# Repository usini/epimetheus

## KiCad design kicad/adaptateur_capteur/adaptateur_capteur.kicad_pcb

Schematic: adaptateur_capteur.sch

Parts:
J1: AudioJack4; Jack_3.5mm_PJ31060-I_Horizontal
JP1: Adresse 1; SolderJumper-2_P1.3mm_Open_TrianglePad1.0x1.5mm
JP2: Adresse 2; SolderJumper-2_P1.3mm_Open_TrianglePad1.0x1.5mm
U1: BME680

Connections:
GND: J1.S, JP1.1, U1.2
unnamed: J1.R1, U1.3
unnamed: J1.R2, U1.4
unnamed: J1.T, JP2.1, U1.1
unnamed: JP1.2, JP2.2, U1.5

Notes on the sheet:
Changement Adresse I²C - SD0 <-> GND 0x76 SD0 <-> VCC 0x77

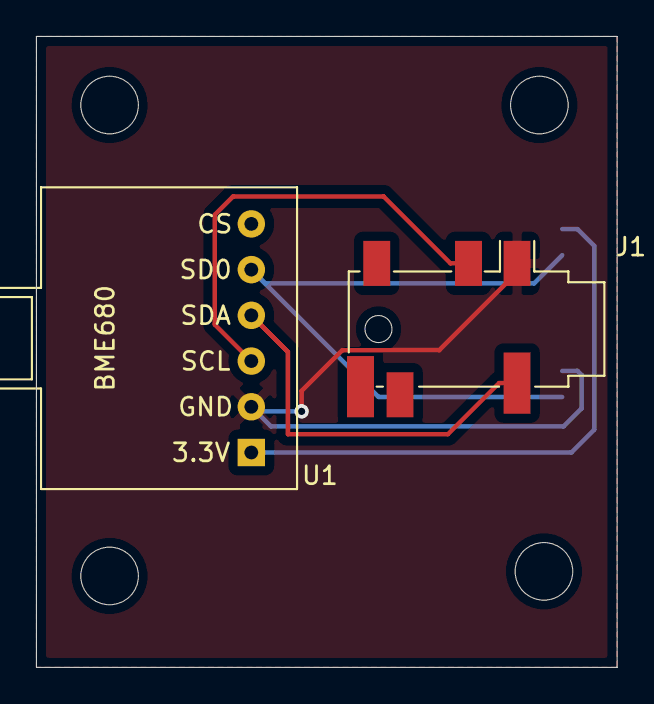
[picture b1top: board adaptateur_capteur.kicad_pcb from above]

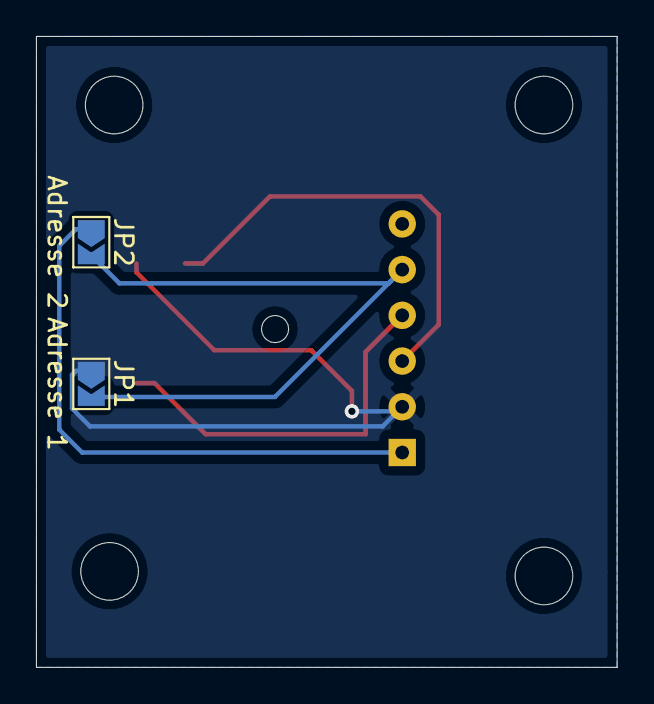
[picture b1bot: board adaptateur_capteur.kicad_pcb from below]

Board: 2 copper layers, 32.3 x 35.1 mm, 4 parts (2 on the bottom side), 5 nets.

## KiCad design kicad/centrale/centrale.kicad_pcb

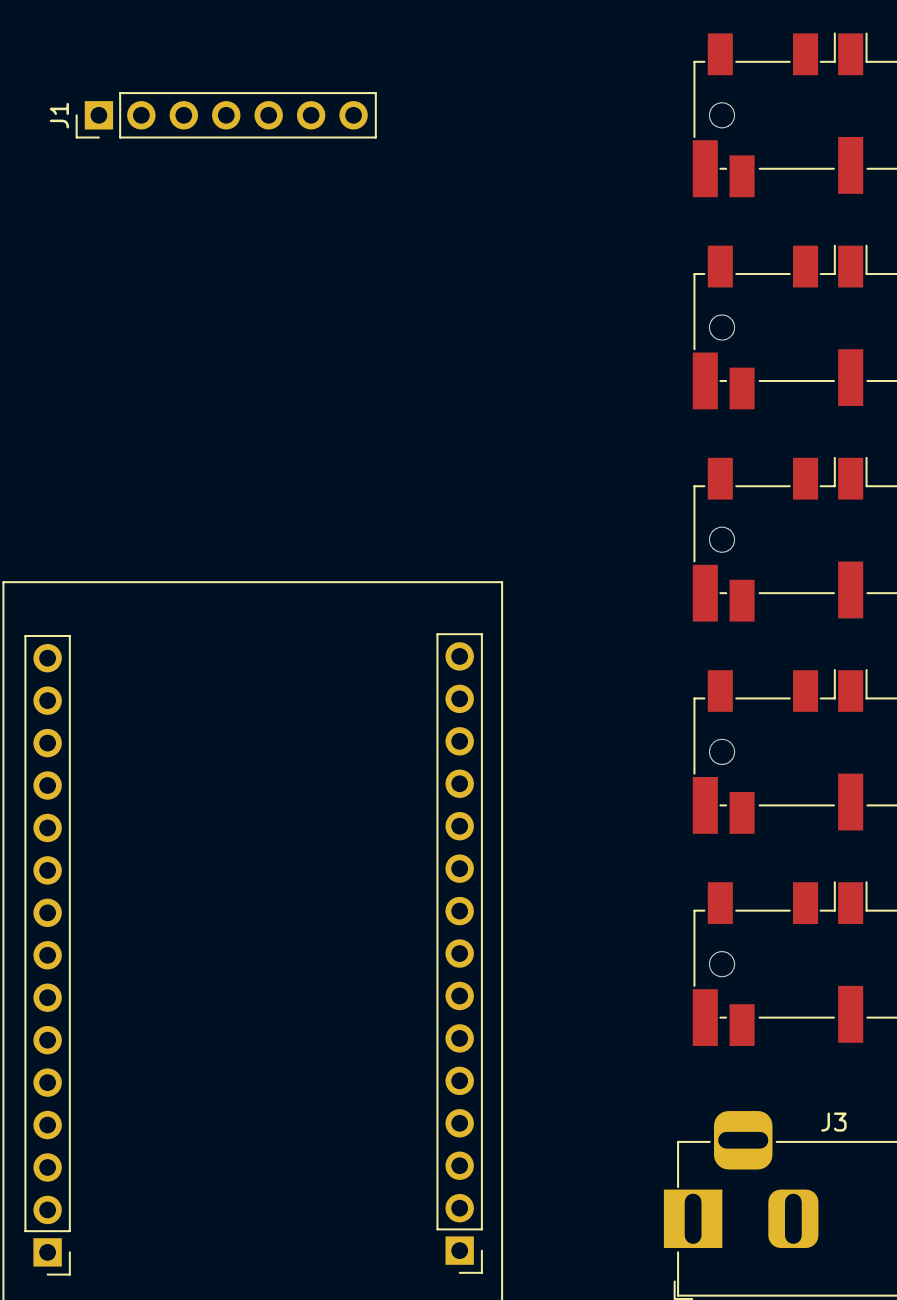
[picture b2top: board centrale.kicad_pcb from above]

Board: 2 copper layers, 8 parts (0 on the bottom side), 9 nets, no tracks yet.

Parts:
J1: SPI (Screen); PinHeader_1x07_P2.54mm_Vertical
J3: 12V Barrel Jack; BarrelJack_Horizontal
J5, J6, J7, J8, J9: AudioJack4; Jack_3.5mm_PJ31060-I_Horizontal
U3: ESP32 Dev Kit; esp32_doit

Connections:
BLK: J1.7, U3.25
DC: J1.6, U3.4
GND: J1.1, J3.2, J5.S, J6.S, J7.S, J8.S, J9.S, U3.2, U3.16
MOSI: J1.4, U3.15
RST: J1.5, U3.8
SCL: J5.R1, J6.R1, J7.R1, J8.R1, J9.R1, U3.14
SCLK: J1.3, U3.9
SDA: J5.R2, J6.R2, J7.R2, J8.R2, J9.R2, U3.11
VCC: J1.2, J5.T, J6.T, J7.T, J8.T, J9.T, U3.1

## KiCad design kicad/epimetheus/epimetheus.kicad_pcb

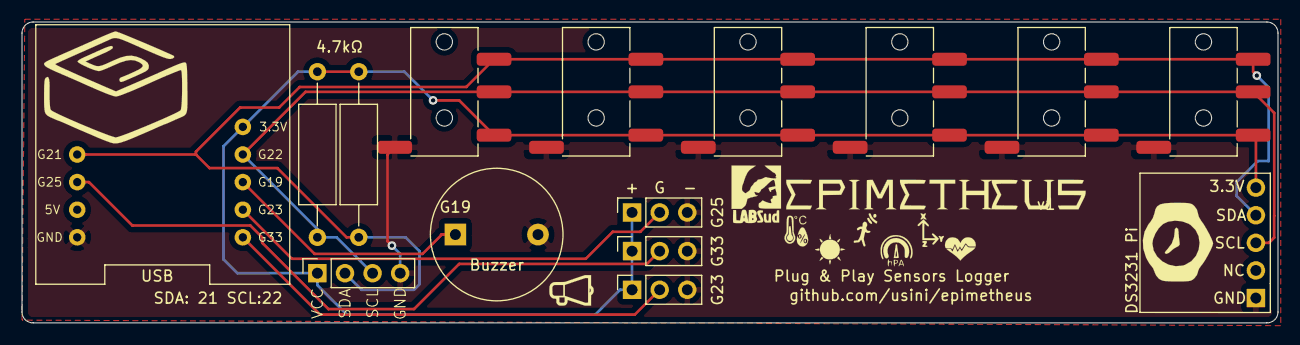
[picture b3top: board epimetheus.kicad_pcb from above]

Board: 2 copper layers, 115.6 x 27.7 mm, 20 parts (0 on the bottom side), 8 nets.

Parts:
BZ1: Buzzer; Buzzer_12x9.5RM7.6
J1: DS3231 (Clock); DS3231_for_Pi
J2, J5, J6, J7, J8, J9: AudioJack4; Jack_3.5mm_TRRS
J3: I2C; PinSocket_1x04_P2.54mm_Vertical
J4: G25; PinSocket_1x03_P2.54mm_Vertical
J10: G23; PinSocket_1x03_P2.54mm_Vertical
J11: G33; PinSocket_1x03_P2.54mm_Vertical
L1: LOGO; speaker_icon
L2: LOGO; clock_logo
L3: LOGO; m5stack_logo
L4: LOGO; sensors_logo
L5: LOGO; epimetheus_logo_large
R1, R2: 4.7kΩ; R_Axial_DIN0309_L9.0mm_D3.2mm_P15.24mm_Horizontal
U1: M5_ATOM_MATRIX; M5_ATOM_MATRIX_ESP32

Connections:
+3V3: J1.5, J2.T, J3.1, J4.1, J5.T, J6.T, J7.T, J8.T, J9.T, J10.1, J11.1, R1.1, R2.2, U1.5
G23: J4.2, U1.8
G25: J11.2, U1.2
G33: J10.2, U1.9
GND: BZ1.2, J1.1, J2.S, J3.4, J4.3, J5.S, J6.S, J7.S, J8.S, J9.S, J10.3, J11.3, U1.4
unnamed: BZ1.1, U1.7
SCL: J1.3, J2.R1, J3.3, J5.R1, J6.R1, J7.R1, J8.R1, J9.R1, R2.1, U1.6
SDA: J1.4, J2.R2, J3.2, J5.R2, J6.R2, J7.R2, J8.R2, J9.R2, R1.2, U1.1

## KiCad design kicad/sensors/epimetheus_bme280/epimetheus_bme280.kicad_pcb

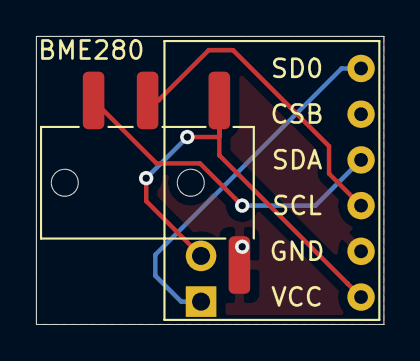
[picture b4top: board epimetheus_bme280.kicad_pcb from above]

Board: 2 copper layers, 19.3 x 16.0 mm, 4 parts (1 on the bottom side), 5 nets.

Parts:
J1: AudioJack4; jack_3.5mm_TRRS
J2: Jumper Address; PinHeader_1x02_P2.54mm_Vertical
L1: LOGO; temp_hum_baro_logo
U1: module_bme280

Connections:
+3V3: J1.T, J2.2, U1.1
GND: J1.S, U1.2
SCL: J1.R1, U1.3
SD0: J2.1, U1.6
SDA: J1.R2, U1.4
